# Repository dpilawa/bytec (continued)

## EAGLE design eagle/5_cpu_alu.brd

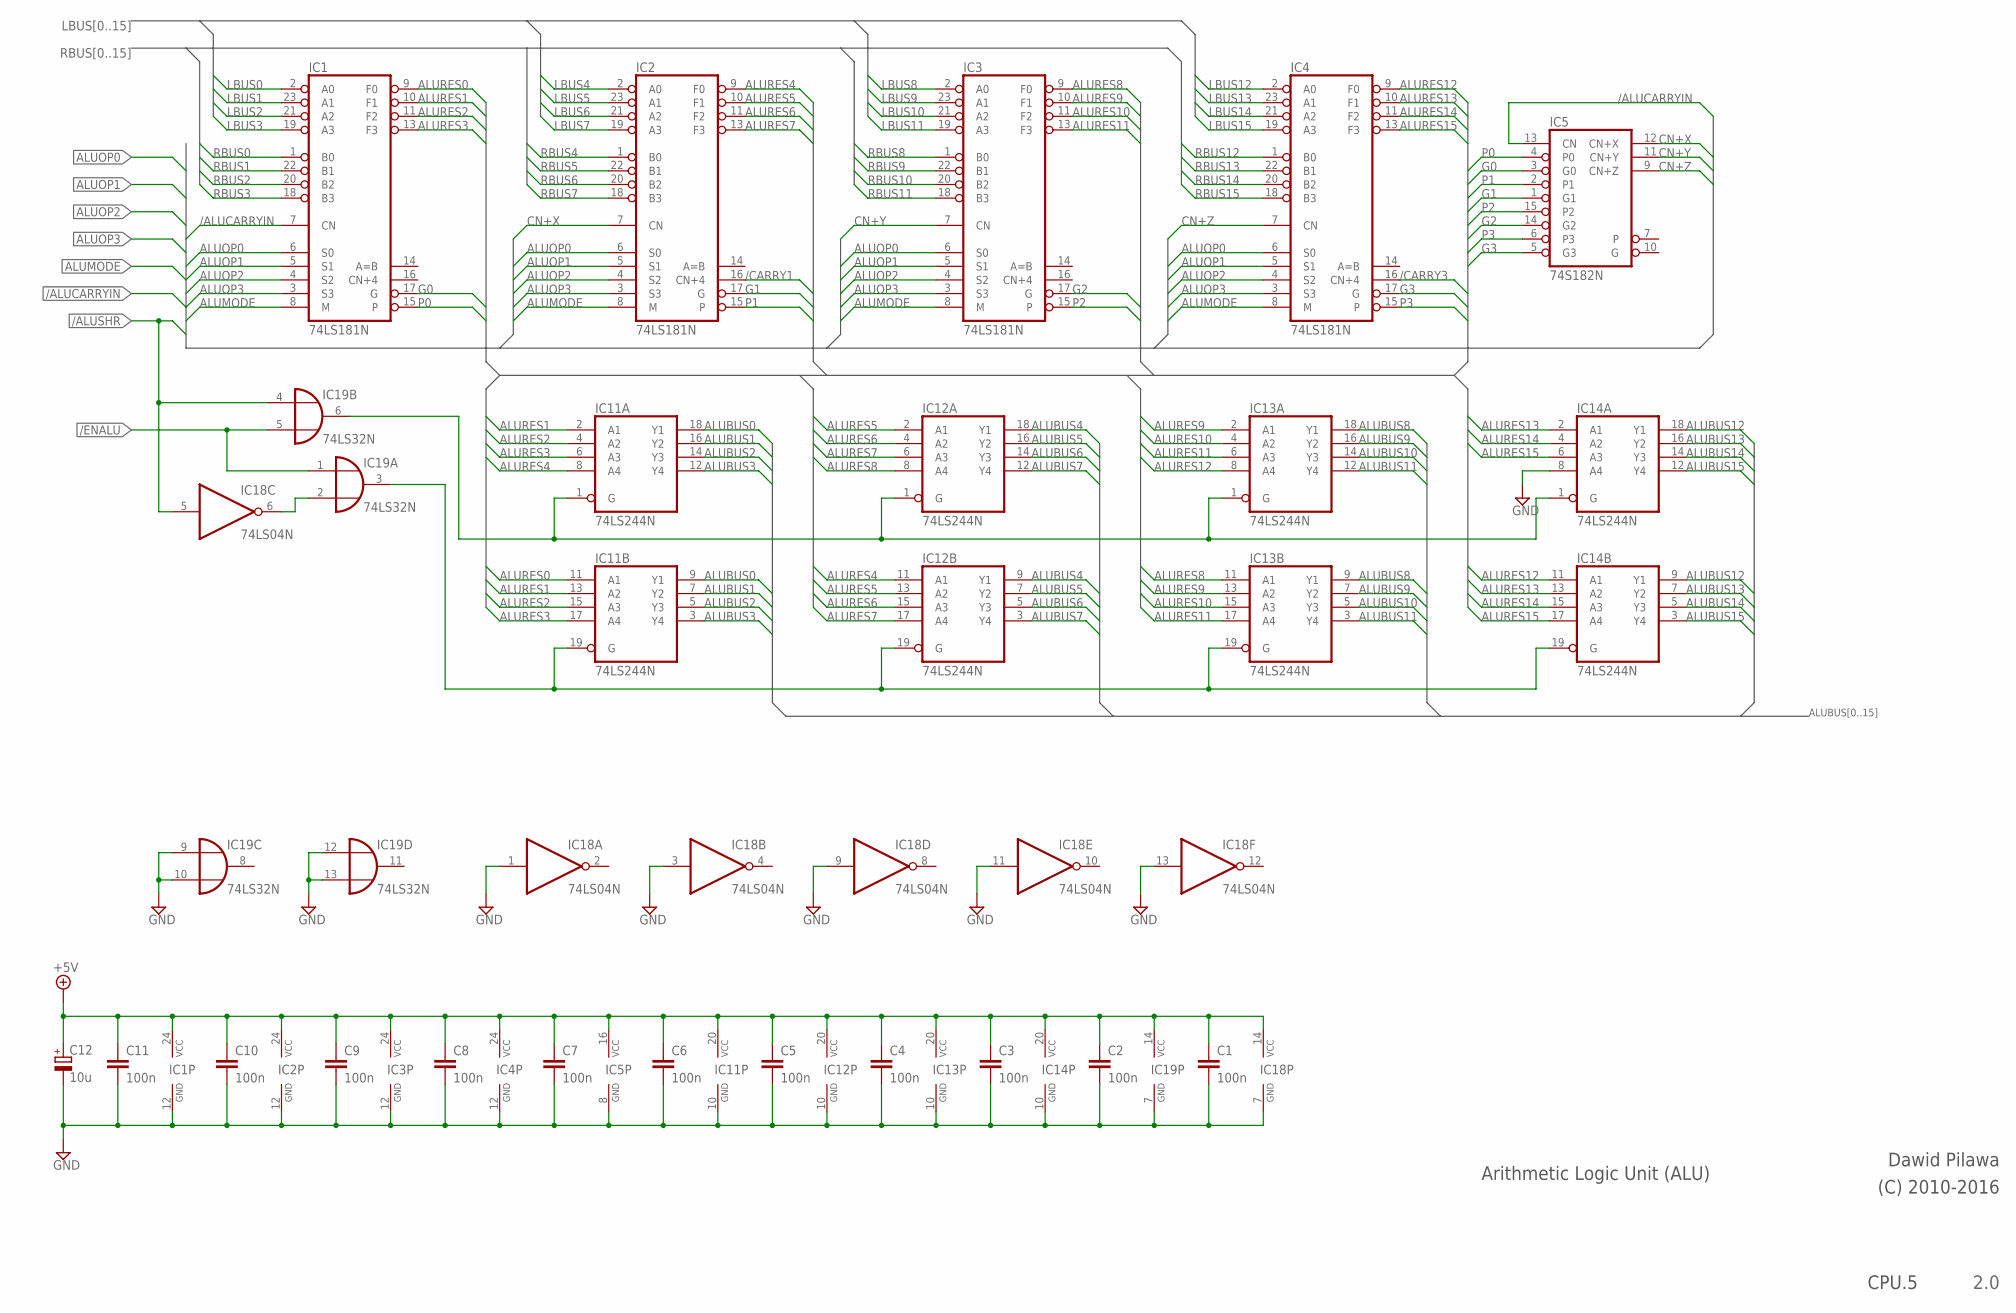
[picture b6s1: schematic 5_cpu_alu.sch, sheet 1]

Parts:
C1, C2, C3, C4, C5, C6, C7, C8, C9, C10, C11: 100n; C050-024X044
C12: 10u; E2,5-6
IC1, IC2, IC3, IC4: 74LS181N; DIL24-6
IC5: 74S182N; DIL16
IC11, IC12, IC13, IC14: 74LS244N; DIL20
IC18: 74LS04N; DIL14
IC19: 74LS32N; DIL14

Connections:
+5V: C1.1, C2.1, C3.1, C4.1, C5.1, C6.1, C7.1, C8.1, C9.1, C10.1, C11.1, C12.+, IC1.24 (VCC), IC2.24 (VCC), IC3.24 (VCC), IC4.24 (VCC), IC5.16 (VCC), IC11.20 (VCC), IC12.20 (VCC), IC13.20 (VCC), IC14.20 (VCC), IC18.14 (VCC), IC19.14 (VCC); also elsewhere on the board
/ALUCARRYIN: IC1.7 (CN), IC5.13 (CN); also elsewhere on the board
/ALUSHR: IC18.5 (I), IC19.4 (I0); also elsewhere on the board
/CARRY1: IC2.16 (CN+4); also elsewhere on the board
/CARRY3: IC4.16 (CN+4); also elsewhere on the board
/ENALU: IC19.1 (I0), IC19.5 (I1); also elsewhere on the board
ALUBUS0: IC11.9 (Y1), IC11.18 (Y1); also elsewhere on the board
ALUBUS1: IC11.7 (Y2), IC11.16 (Y2); also elsewhere on the board
ALUBUS2: IC11.5 (Y3), IC11.14 (Y3); also elsewhere on the board
ALUBUS3: IC11.3 (Y4), IC11.12 (Y4); also elsewhere on the board
ALUBUS4: IC12.9 (Y1), IC12.18 (Y1); also elsewhere on the board
ALUBUS5: IC12.7 (Y2), IC12.16 (Y2); also elsewhere on the board
ALUBUS6: IC12.5 (Y3), IC12.14 (Y3); also elsewhere on the board
ALUBUS7: IC12.3 (Y4), IC12.12 (Y4); also elsewhere on the board
ALUBUS8: IC13.9 (Y1), IC13.18 (Y1); also elsewhere on the board
ALUBUS9: IC13.7 (Y2), IC13.16 (Y2); also elsewhere on the board
ALUBUS10: IC13.5 (Y3), IC13.14 (Y3); also elsewhere on the board
ALUBUS11: IC13.3 (Y4), IC13.12 (Y4); also elsewhere on the board
ALUBUS12: IC14.9 (Y1), IC14.18 (Y1); also elsewhere on the board
ALUBUS13: IC14.7 (Y2), IC14.16 (Y2); also elsewhere on the board
ALUBUS14: IC14.5 (Y3), IC14.14 (Y3); also elsewhere on the board
ALUBUS15: IC14.3 (Y4), IC14.12 (Y4); also elsewhere on the board
ALUMODE: IC1.8 (M), IC2.8 (M), IC3.8 (M), IC4.8 (M); also elsewhere on the board
ALUOP0: IC1.6 (S0), IC2.6 (S0), IC3.6 (S0), IC4.6 (S0); also elsewhere on the board
ALUOP1: IC1.5 (S1), IC2.5 (S1), IC3.5 (S1), IC4.5 (S1); also elsewhere on the board
ALUOP2: IC1.4 (S2), IC2.4 (S2), IC3.4 (S2), IC4.4 (S2); also elsewhere on the board
ALUOP3: IC1.3 (S3), IC2.3 (S3), IC3.3 (S3), IC4.3 (S3); also elsewhere on the board
ALURES0: IC1.9 (F0), IC11.11 (A1); also elsewhere on the board
ALURES1: IC1.10 (F1), IC11.2 (A1), IC11.13 (A2)
ALURES2: IC1.11 (F2), IC11.4 (A2), IC11.15 (A3)
ALURES3: IC1.13 (F3), IC11.6 (A3), IC11.17 (A4)
ALURES4: IC2.9 (F0), IC11.8 (A4), IC12.11 (A1)
ALURES5: IC2.10 (F1), IC12.2 (A1), IC12.13 (A2)
ALURES6: IC2.11 (F2), IC12.4 (A2), IC12.15 (A3)
ALURES7: IC2.13 (F3), IC12.6 (A3), IC12.17 (A4)
ALURES8: IC3.9 (F0), IC12.8 (A4), IC13.11 (A1); also elsewhere on the board
ALURES9: IC3.10 (F1), IC13.2 (A1), IC13.13 (A2)
ALURES10: IC3.11 (F2), IC13.4 (A2), IC13.15 (A3)
ALURES11: IC3.13 (F3), IC13.6 (A3), IC13.17 (A4)
ALURES12: IC4.9 (F0), IC13.8 (A4), IC14.11 (A1)
ALURES13: IC4.10 (F1), IC14.2 (A1), IC14.13 (A2)
ALURES14: IC4.11 (F2), IC14.4 (A2), IC14.15 (A3)
ALURES15: IC4.13 (F3), IC14.6 (A3), IC14.17 (A4)
CN+X: IC2.7 (CN), IC5.12 (CN+X)
CN+Y: IC3.7 (CN), IC5.11 (CN+Y)
CN+Z: IC4.7 (CN), IC5.9 (CN+Z)
G0: IC1.17 (G), IC5.3 (G0)
G1: IC2.17 (G), IC5.1 (G1)
G2: IC3.17 (G), IC5.14 (G2)
G3: IC4.17 (G), IC5.5 (G3)
GND: C1.2, C2.2, C3.2, C4.2, C5.2, C6.2, C7.2, C8.2, C9.2, C10.2, C11.2, C12.-, IC1.12 (GND), IC2.12 (GND), IC3.12 (GND), IC4.12 (GND), IC5.8 (GND), IC11.10 (GND), IC12.10 (GND), IC13.10 (GND), IC14.8 (A4), IC14.10 (GND), IC18.1 (I), IC18.3 (I), IC18.7 (GND), IC18.9 (I), IC18.11 (I), IC18.13 (I), IC19.7 (GND), IC19.9 (I0), IC19.10 (I1), IC19.12 (I0), IC19.13 (I1); also elsewhere on the board
LBUS0: IC1.2 (A0); also elsewhere on the board
LBUS1: IC1.23 (A1); also elsewhere on the board
LBUS2: IC1.21 (A2); also elsewhere on the board
LBUS3: IC1.19 (A3); also elsewhere on the board
LBUS4: IC2.2 (A0); also elsewhere on the board
LBUS5: IC2.23 (A1); also elsewhere on the board
LBUS6: IC2.21 (A2); also elsewhere on the board
LBUS7: IC2.19 (A3); also elsewhere on the board
LBUS8: IC3.2 (A0); also elsewhere on the board
LBUS9: IC3.23 (A1); also elsewhere on the board
LBUS10: IC3.21 (A2); also elsewhere on the board
LBUS11: IC3.19 (A3); also elsewhere on the board
LBUS12: IC4.2 (A0); also elsewhere on the board
LBUS13: IC4.23 (A1); also elsewhere on the board
LBUS14: IC4.21 (A2); also elsewhere on the board
LBUS15: IC4.19 (A3); also elsewhere on the board
unnamed: IC11.1 (G), IC12.1 (G), IC13.1 (G), IC14.1 (G), IC19.6 (O)
unnamed: IC18.6 (O), IC19.2 (I1)
unnamed: IC11.19 (G), IC12.19 (G), IC13.19 (G), IC14.19 (G), IC19.3 (O)
P0: IC1.15, IC5.4 (P0)
P1: IC2.15, IC5.2 (P1)
P2: IC3.15, IC5.15 (P2)
P3: IC4.15, IC5.6 (P3)
RBUS0: IC1.1 (B0); also elsewhere on the board
RBUS1: IC1.22 (B1); also elsewhere on the board
RBUS2: IC1.20 (B2); also elsewhere on the board
RBUS3: IC1.18 (B3); also elsewhere on the board
RBUS4: IC2.1 (B0); also elsewhere on the board
RBUS5: IC2.22 (B1); also elsewhere on the board
RBUS6: IC2.20 (B2); also elsewhere on the board
RBUS7: IC2.18 (B3); also elsewhere on the board
RBUS8: IC3.1 (B0); also elsewhere on the board
RBUS9: IC3.22 (B1); also elsewhere on the board
RBUS10: IC3.20 (B2); also elsewhere on the board
RBUS11: IC3.18 (B3); also elsewhere on the board
RBUS12: IC4.1 (B0); also elsewhere on the board
RBUS13: IC4.22 (B1); also elsewhere on the board
RBUS14: IC4.20 (B2); also elsewhere on the board
RBUS15: IC4.18 (B3); also elsewhere on the board

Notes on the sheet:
Arithmetic Logic Unit (ALU)
Dawid Pilawa
(C) 2010-2016
2.0
CPU.5

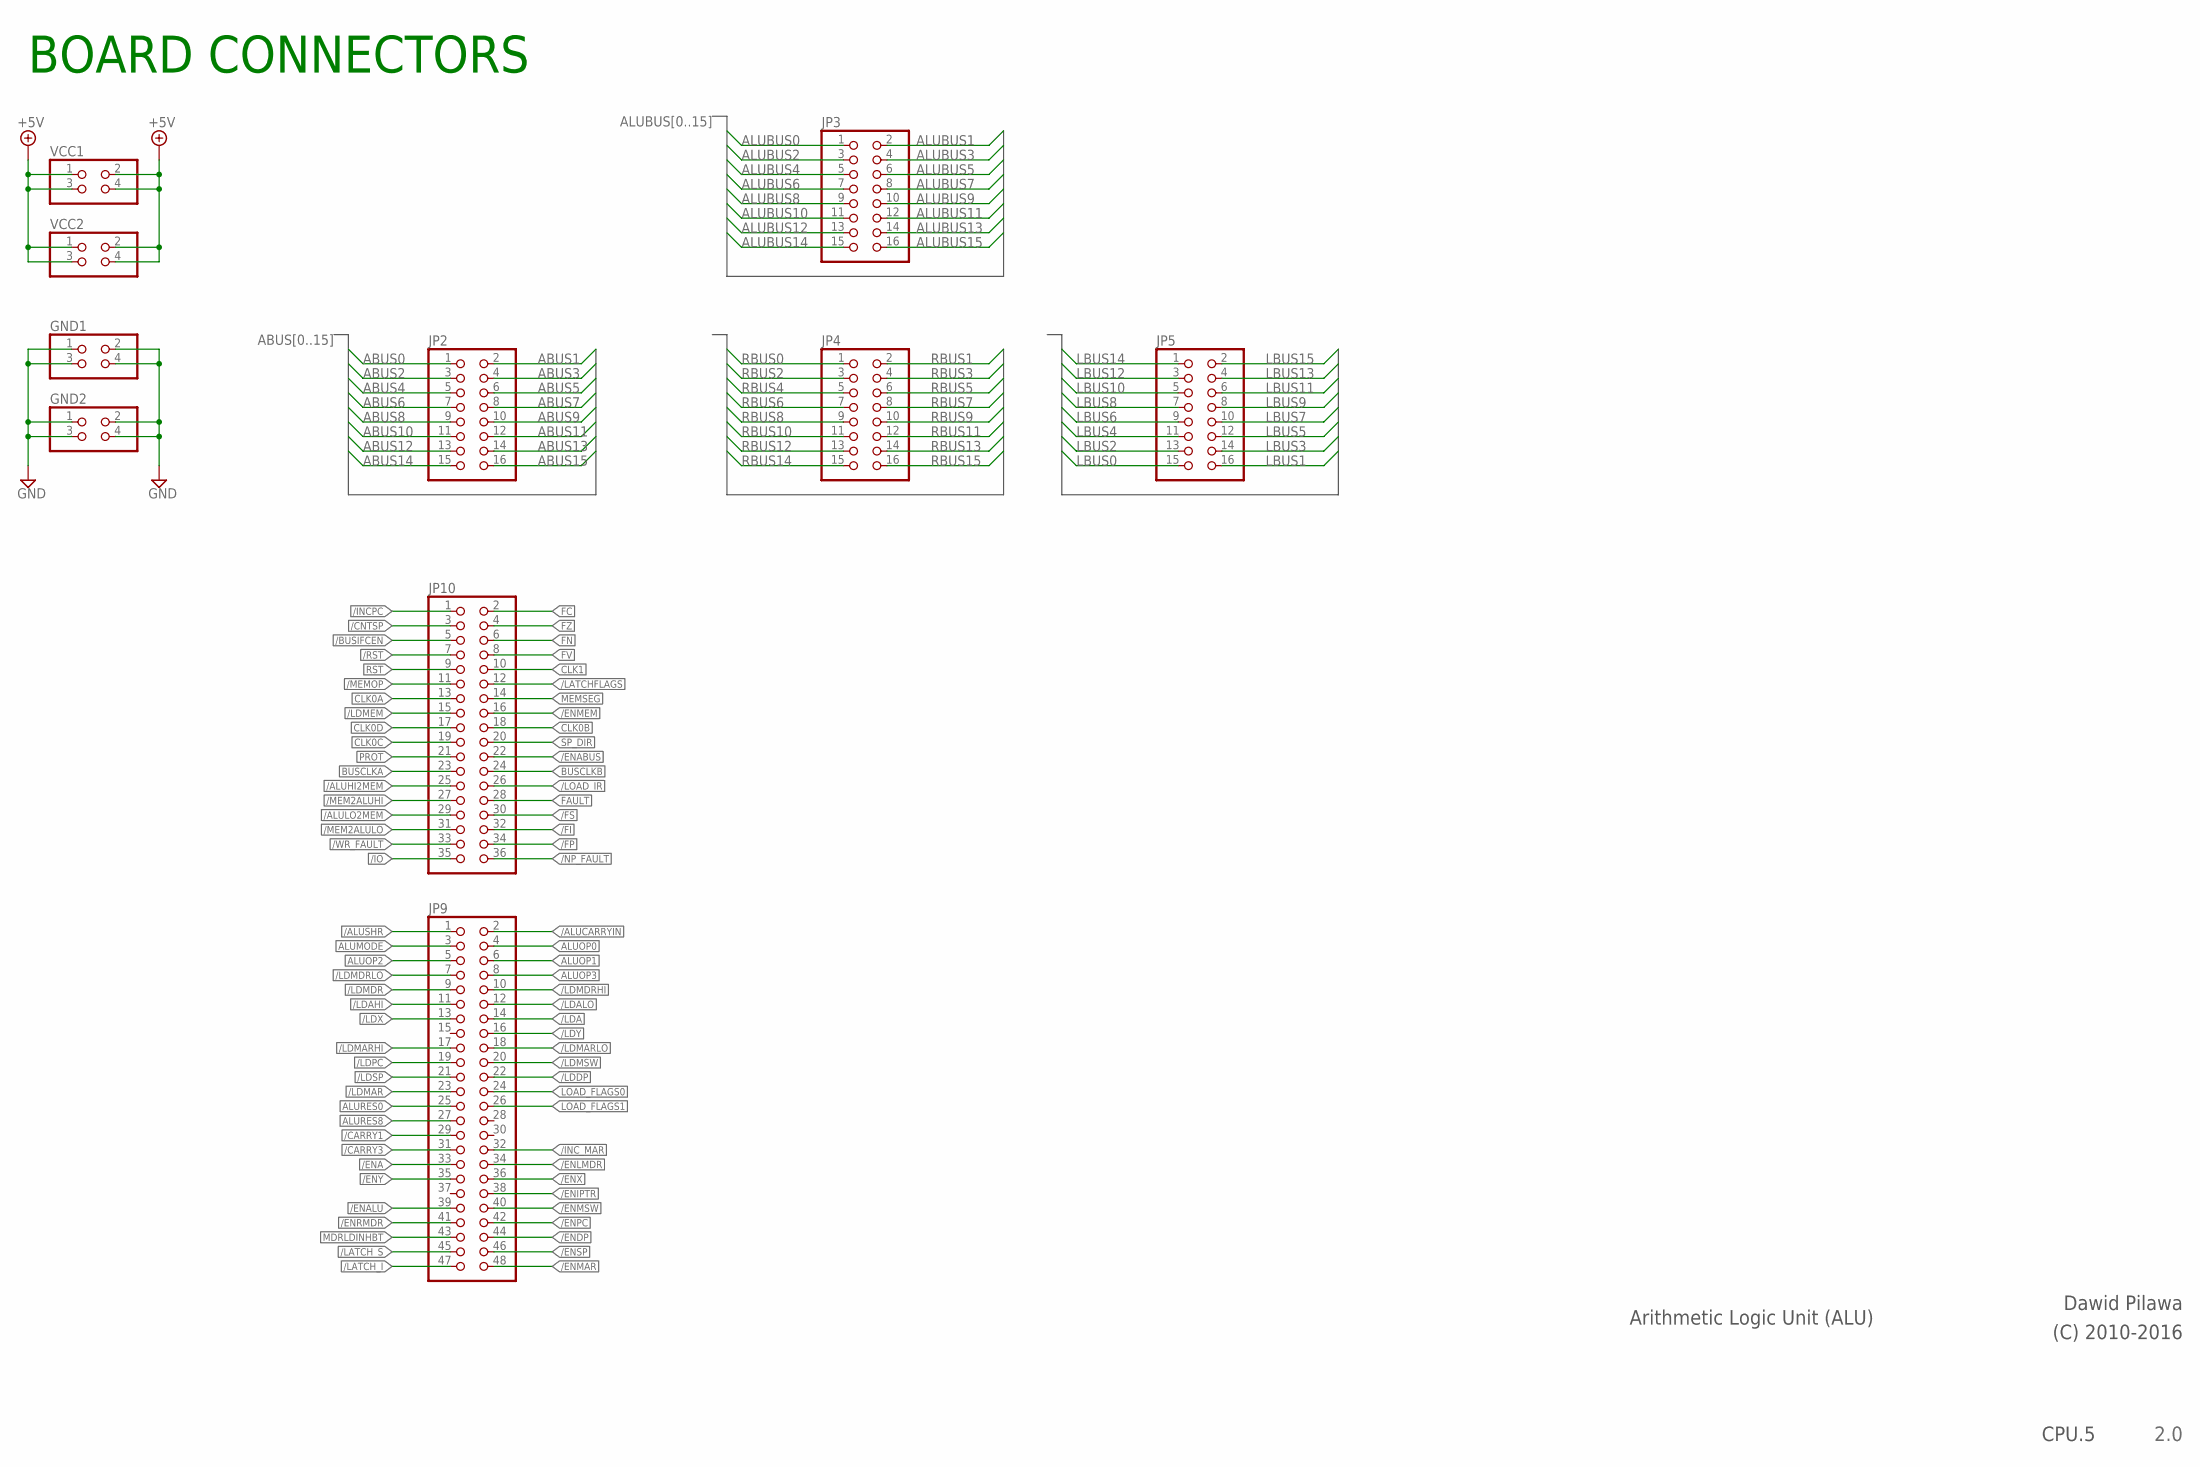
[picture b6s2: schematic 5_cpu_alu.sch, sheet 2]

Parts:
GND1, GND2: PINHD-2X2; 2X02
JP2, JP3, JP4, JP5: PINHD-2X8; 2X08
JP9: PINHD-2X24; 2X24
JP10: PINHD-2X18; 2X18
VCC1, VCC2: PINHD-2X2; 2X02

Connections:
+5V: VCC1.1, VCC1.2, VCC1.3, VCC1.4, VCC2.1, VCC2.2, VCC2.3, VCC2.4; also elsewhere on the board
/ALUCARRYIN: JP9.2; also elsewhere on the board
/ALUHI2MEM: JP10.25
/ALULO2MEM: JP10.29
/ALUSHR: JP9.1; also elsewhere on the board
/BUSIFCEN: JP10.5
/CARRY1: JP9.29; also elsewhere on the board
/CARRY3: JP9.31; also elsewhere on the board
/CNTSP: JP10.3
/ENA: JP9.33
/ENABUS: JP10.22
/ENALU: JP9.39; also elsewhere on the board
/ENDP: JP9.44
/ENIPTR: JP9.38
/ENLMDR: JP9.34
/ENMAR: JP9.48
/ENMEM: JP10.16
/ENMSW: JP9.40
/ENPC: JP9.42
/ENRMDR: JP9.41
/ENSP: JP9.46
/ENX: JP9.36
/ENY: JP9.35
/FI: JP10.32
/FP: JP10.34
/FS: JP10.30
/INCPC: JP10.1
/INC_MAR: JP9.32
/IO: JP10.35
/LATCHFLAGS: JP10.12
/LATCH_I: JP9.47
/LATCH_S: JP9.45
/LDA: JP9.14
/LDAHI: JP9.11
/LDALO: JP9.12
/LDDP: JP9.22
/LDMAR: JP9.23
/LDMARHI: JP9.17
/LDMARLO: JP9.18
/LDMDR: JP9.9
/LDMDRHI: JP9.10
/LDMDRLO: JP9.7
/LDMEM: JP10.15
/LDMSW: JP9.20
/LDPC: JP9.19
/LDSP: JP9.21
/LDX: JP9.13
/LDY: JP9.16
/LOAD_IR: JP10.26
/MEM2ALUHI: JP10.27
/MEM2ALULO: JP10.31
/MEMOP: JP10.11
/NP_FAULT: JP10.36
/RST: JP10.7
/WR_FAULT: JP10.33
ABUS0: JP2.1
ABUS1: JP2.2
ABUS2: JP2.3
ABUS3: JP2.4
ABUS4: JP2.5
ABUS5: JP2.6
ABUS6: JP2.7
ABUS7: JP2.8
ABUS8: JP2.9
ABUS9: JP2.10
ABUS10: JP2.11
ABUS11: JP2.12
ABUS12: JP2.13
ABUS13: JP2.14
ABUS14: JP2.15
ABUS15: JP2.16
ALUBUS0: JP3.1; also elsewhere on the board
ALUBUS1: JP3.2; also elsewhere on the board
ALUBUS2: JP3.3; also elsewhere on the board
ALUBUS3: JP3.4; also elsewhere on the board
ALUBUS4: JP3.5; also elsewhere on the board
ALUBUS5: JP3.6; also elsewhere on the board
ALUBUS6: JP3.7; also elsewhere on the board
ALUBUS7: JP3.8; also elsewhere on the board
ALUBUS8: JP3.9; also elsewhere on the board
ALUBUS9: JP3.10; also elsewhere on the board
ALUBUS10: JP3.11; also elsewhere on the board
ALUBUS11: JP3.12; also elsewhere on the board
ALUBUS12: JP3.13; also elsewhere on the board
ALUBUS13: JP3.14; also elsewhere on the board
ALUBUS14: JP3.15; also elsewhere on the board
ALUBUS15: JP3.16; also elsewhere on the board
ALUMODE: JP9.3; also elsewhere on the board
ALUOP0: JP9.4; also elsewhere on the board
ALUOP1: JP9.6; also elsewhere on the board
ALUOP2: JP9.5; also elsewhere on the board
ALUOP3: JP9.8; also elsewhere on the board
ALURES0: JP9.25; also elsewhere on the board
ALURES8: JP9.27; also elsewhere on the board
BUSCLKA: JP10.23
BUSCLKB: JP10.24
CLK0A: JP10.13
CLK0B: JP10.18
CLK0C: JP10.19
CLK0D: JP10.17
CLK1: JP10.10
FAULT: JP10.28
FC: JP10.2
FN: JP10.6
FV: JP10.8
FZ: JP10.4
GND: GND1.1, GND1.2, GND1.3, GND1.4, GND2.1, GND2.2, GND2.3, GND2.4; also elsewhere on the board
LBUS0: JP5.15; also elsewhere on the board
LBUS1: JP5.16; also elsewhere on the board
LBUS2: JP5.13; also elsewhere on the board
LBUS3: JP5.14; also elsewhere on the board
LBUS4: JP5.11; also elsewhere on the board
LBUS5: JP5.12; also elsewhere on the board
LBUS6: JP5.9; also elsewhere on the board
LBUS7: JP5.10; also elsewhere on the board
LBUS8: JP5.7; also elsewhere on the board
LBUS9: JP5.8; also elsewhere on the board
LBUS10: JP5.5; also elsewhere on the board
LBUS11: JP5.6; also elsewhere on the board
LBUS12: JP5.3; also elsewhere on the board
LBUS13: JP5.4; also elsewhere on the board
LBUS14: JP5.1; also elsewhere on the board
LBUS15: JP5.2; also elsewhere on the board
LOAD_FLAGS0: JP9.24
LOAD_FLAGS1: JP9.26
MDRLDINHBT: JP9.43
MEMSEG: JP10.14
PROT: JP10.21
RBUS0: JP4.1; also elsewhere on the board
RBUS1: JP4.2; also elsewhere on the board
RBUS2: JP4.3; also elsewhere on the board
RBUS3: JP4.4; also elsewhere on the board
RBUS4: JP4.5; also elsewhere on the board
RBUS5: JP4.6; also elsewhere on the board
RBUS6: JP4.7; also elsewhere on the board
RBUS7: JP4.8; also elsewhere on the board
RBUS8: JP4.9; also elsewhere on the board
RBUS9: JP4.10; also elsewhere on the board
RBUS10: JP4.11; also elsewhere on the board
RBUS11: JP4.12; also elsewhere on the board
RBUS12: JP4.13; also elsewhere on the board
RBUS13: JP4.14; also elsewhere on the board
RBUS14: JP4.15; also elsewhere on the board
RBUS15: JP4.16; also elsewhere on the board
RST: JP10.9
SP_DIR: JP10.20

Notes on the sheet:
Arithmetic Logic Unit (ALU)
Dawid Pilawa
(C) 2010-2016
2.0
CPU.5
BOARD CONNECTORS

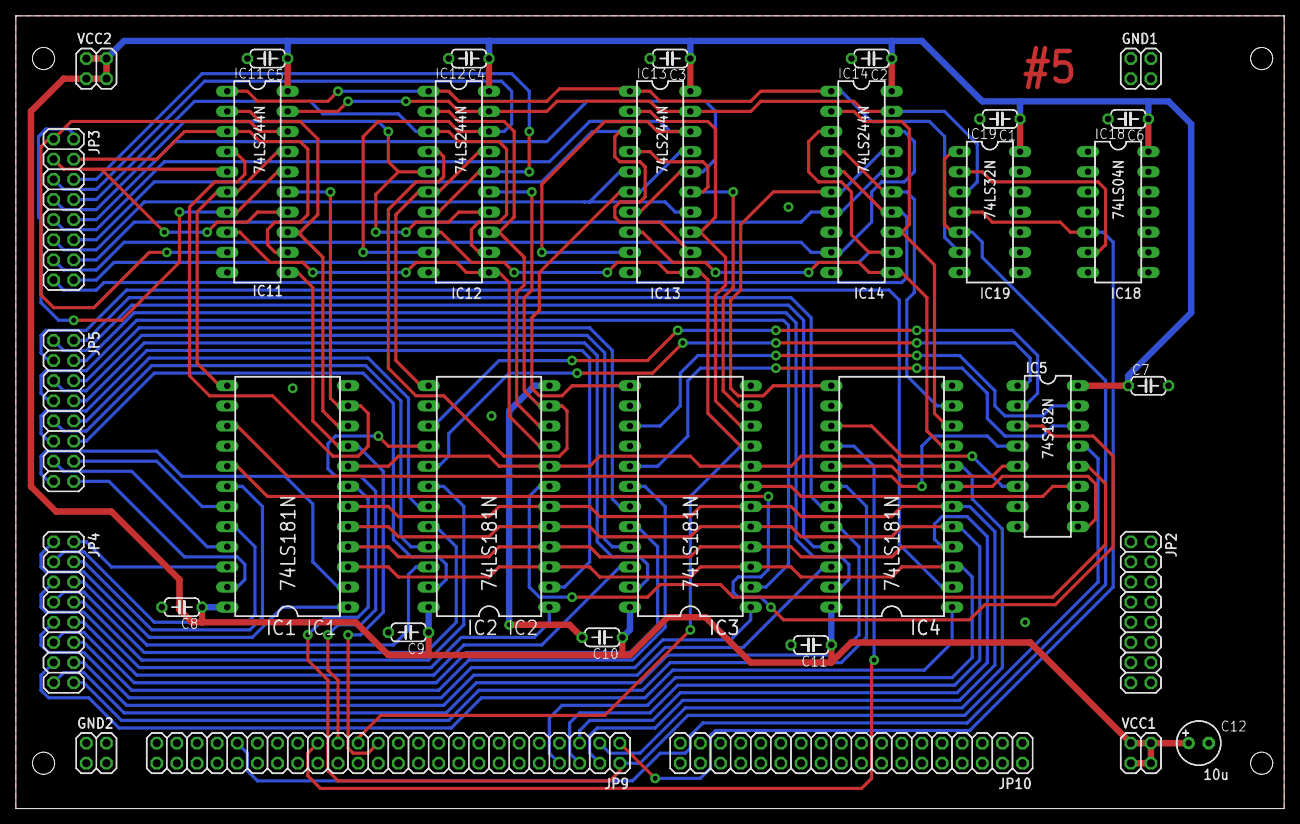
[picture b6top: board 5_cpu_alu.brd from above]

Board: 2 copper layers, 160.0 x 100.0 mm, 33 parts (0 on the bottom side), 90 nets.

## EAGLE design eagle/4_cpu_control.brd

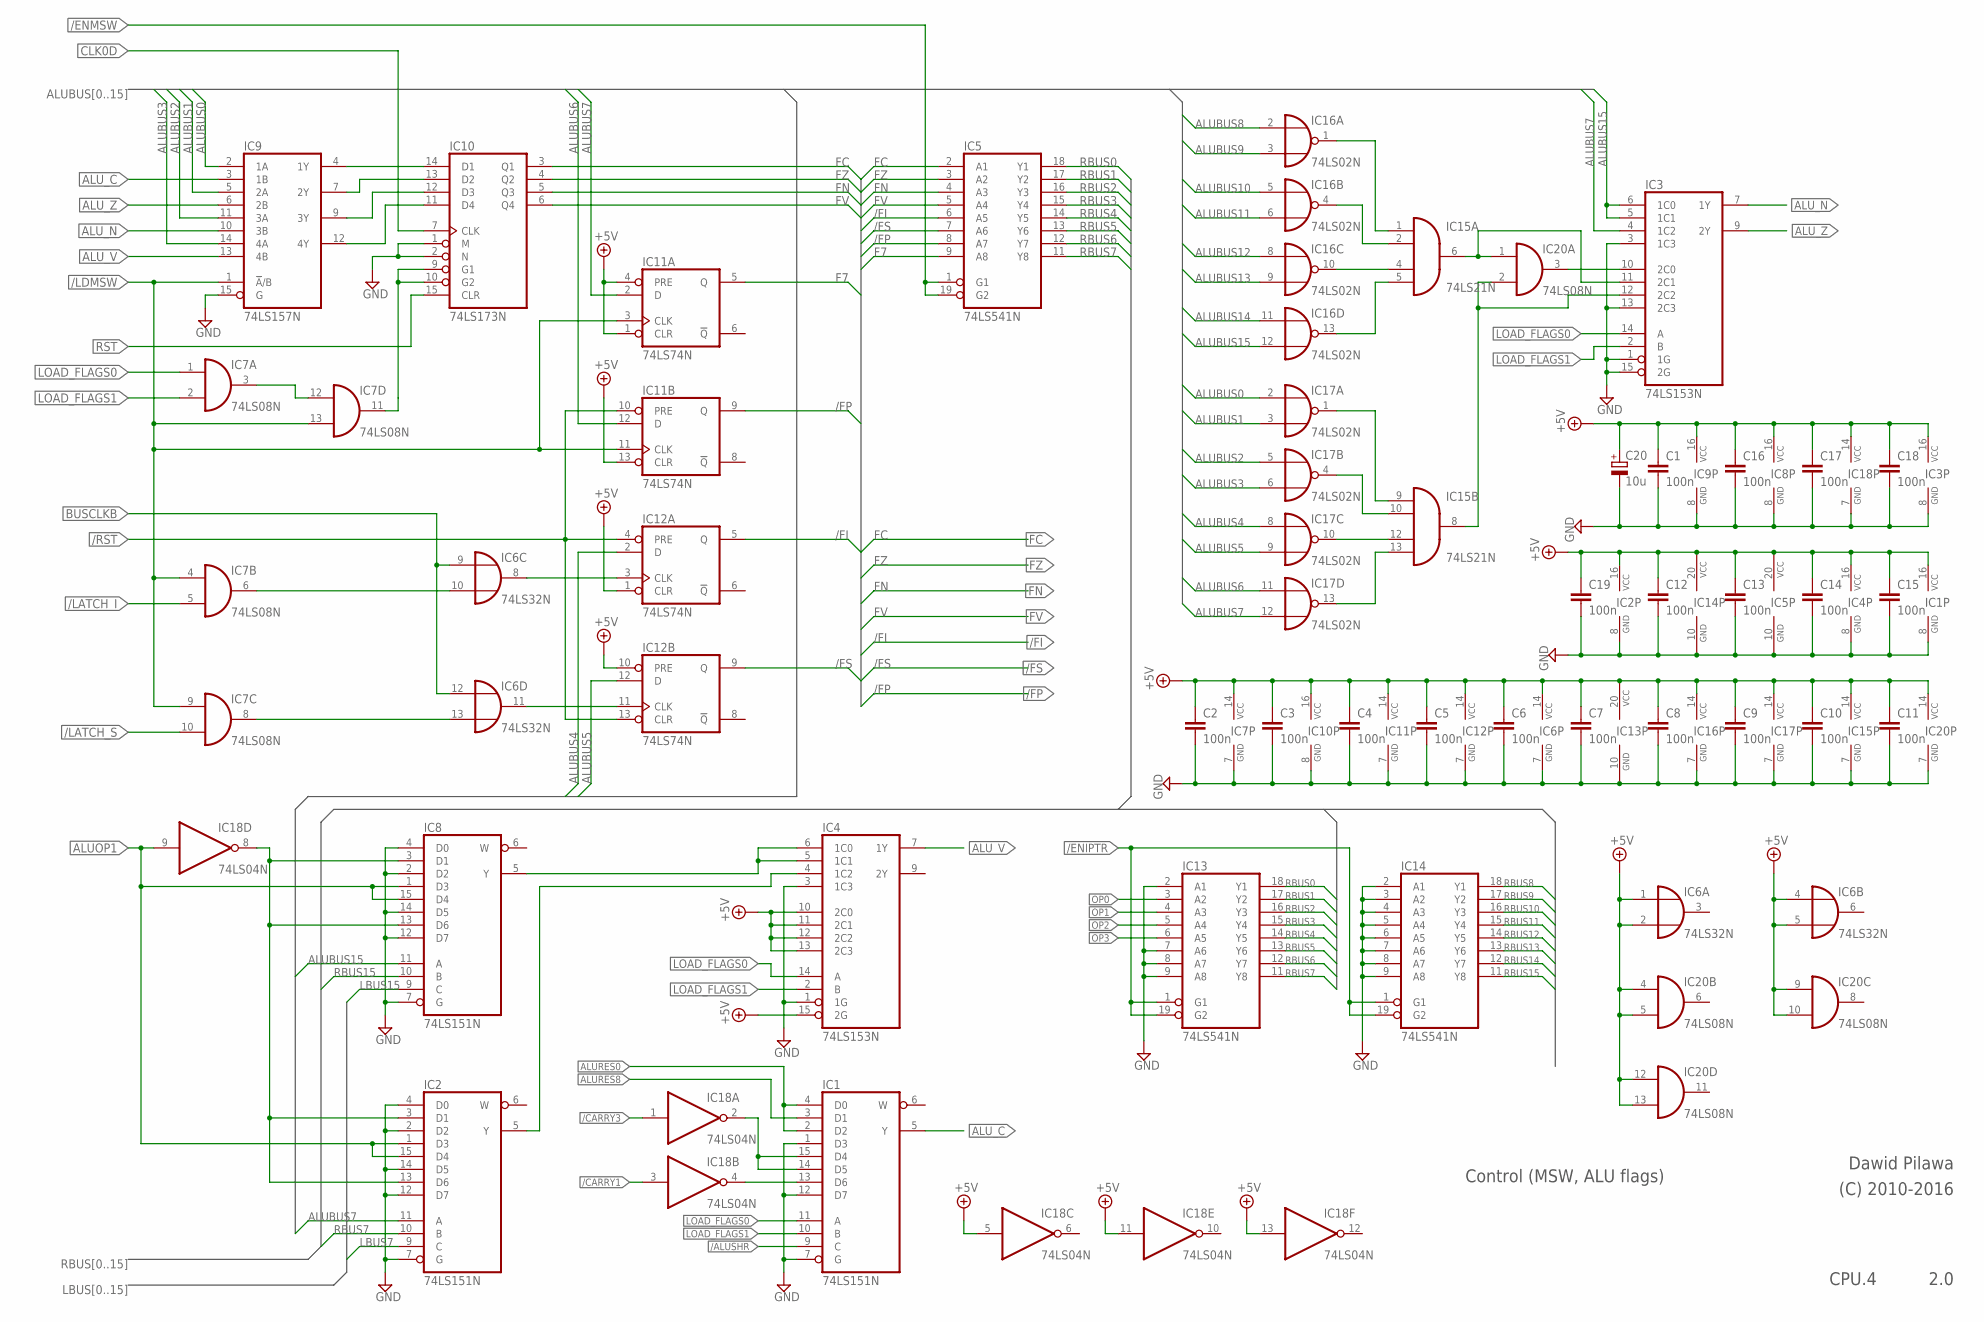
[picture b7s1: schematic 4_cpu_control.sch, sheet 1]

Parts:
C1, C2, C3, C4, C5, C6, C7, C8, C9, C10, C11, C12, C13, C14, C15, C16, C17, C18, C19: 100n; C050-024X044
C20: 10u; E2,5-6
IC1, IC2, IC8: 74LS151N; DIL16
IC3, IC4: 74LS153N; DIL16
IC5, IC13, IC14: 74LS541N; DIL20
IC6: 74LS32N; DIL14
IC7, IC20: 74LS08N; DIL14
IC9: 74LS157N; DIL16
IC10: 74LS173N; DIL16
IC11, IC12: 74LS74N; DIL14
IC15: 74LS21N; DIL14
IC16, IC17: 74LS02N; DIL14
IC18: 74LS04N; DIL14

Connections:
+5V: C1.1, C2.1, C3.1, C4.1, C5.1, C6.1, C7.1, C8.1, C9.1, C10.1, C11.1, C12.1, C13.1, C14.1, C15.1, C16.1, C17.1, C18.1, C19.1, C20.+, IC1.16 (VCC), IC2.16 (VCC), IC3.16 (VCC), IC4.10 (2C0), IC4.11 (2C1), IC4.12 (2C2), IC4.13 (2C3), IC4.15 (2G), IC4.16 (VCC), IC5.20 (VCC), IC6.1 (I0), IC6.2 (I1), IC6.4 (I0), IC6.5 (I1), IC6.14 (VCC), IC7.14 (VCC), IC8.16 (VCC), IC9.16 (VCC), IC10.16 (VCC), IC11.1 (CLR), IC11.4 (PRE), IC11.13 (CLR), IC11.14 (VCC), IC12.1 (CLR), IC12.10 (PRE), IC12.14 (VCC), IC13.20 (VCC), IC14.20 (VCC), IC15.14 (VCC), IC16.14 (VCC), IC17.14 (VCC), IC18.5 (I), IC18.11 (I), IC18.13 (I), IC18.14 (VCC), IC20.4 (I0), IC20.5 (I1), IC20.9 (I0), IC20.10 (I1), IC20.12 (I0), IC20.13 (I1), IC20.14 (VCC); also elsewhere on the board
/ALUSHR: IC1.9 (C); also elsewhere on the board
/CARRY1: IC18.3 (I); also elsewhere on the board
/CARRY3: IC18.1 (I); also elsewhere on the board
/ENIPTR: IC13.1 (G1), IC13.19 (G2), IC14.1 (G1), IC14.19 (G2); also elsewhere on the board
/ENMSW: IC5.1 (G1), IC5.19 (G2); also elsewhere on the board
/FI: IC5.6 (A5), IC12.5 (Q); also elsewhere on the board
/FP: IC5.8 (A7), IC11.9 (Q); also elsewhere on the board
/FS: IC5.7 (A6), IC12.9 (Q); also elsewhere on the board
/LATCH_I: IC7.5 (I1); also elsewhere on the board
/LATCH_S: IC7.10 (I1); also elsewhere on the board
/LDMSW: IC7.4 (I0), IC7.9 (I0), IC7.13 (I1), IC9.1 (!A!/B), IC11.3 (CLK), IC11.11 (CLK); also elsewhere on the board
/RST: IC11.10 (PRE), IC12.4 (PRE), IC12.13 (CLR); also elsewhere on the board
ALUBUS0: IC9.2 (1A), IC17.2 (I0); also elsewhere on the board
ALUBUS1: IC9.5 (2A), IC17.3 (I1); also elsewhere on the board
ALUBUS2: IC9.11 (3A), IC17.5 (I0); also elsewhere on the board
ALUBUS3: IC9.14 (4A), IC17.6 (I1); also elsewhere on the board
ALUBUS4: IC12.2 (D), IC17.8 (I0); also elsewhere on the board
ALUBUS5: IC12.12 (D), IC17.9 (I1); also elsewhere on the board
ALUBUS6: IC11.12 (D), IC17.11 (I0); also elsewhere on the board
ALUBUS7: IC2.11 (A), IC3.4 (1C2), IC11.2 (D), IC17.12 (I1); also elsewhere on the board
ALUBUS8: IC16.2 (I0); also elsewhere on the board
ALUBUS9: IC16.3 (I1); also elsewhere on the board
ALUBUS10: IC16.5 (I0); also elsewhere on the board
ALUBUS11: IC16.6 (I1); also elsewhere on the board
ALUBUS12: IC16.8 (I0); also elsewhere on the board
ALUBUS13: IC16.9 (I1); also elsewhere on the board
ALUBUS14: IC16.11 (I0); also elsewhere on the board
ALUBUS15: IC3.5 (1C1), IC3.6 (1C0), IC8.11 (A), IC16.12 (I1); also elsewhere on the board
ALUOP1: IC2.1 (D3), IC2.15 (D4), IC8.1 (D3), IC8.15 (D4), IC18.9 (I); also elsewhere on the board
ALURES0: IC1.2 (D2), IC1.4 (D0); also elsewhere on the board
ALURES8: IC1.3 (D1); also elsewhere on the board
ALU_C: IC1.5 (Y), IC9.3 (1B)
ALU_N: IC3.7 (1Y), IC9.10 (3B)
ALU_V: IC4.7 (1Y), IC9.13 (4B)
ALU_Z: IC3.9 (2Y), IC9.6 (2B)
BUSCLKB: IC6.9 (I0), IC6.12 (I0); also elsewhere on the board
CLK0D: IC10.7 (CLK); also elsewhere on the board
F7: IC5.9 (A8), IC11.5 (Q)
FC: IC5.2 (A1), IC10.3 (Q1); also elsewhere on the board
FN: IC5.4 (A3), IC10.5 (Q3); also elsewhere on the board
FV: IC5.5 (A4), IC10.6 (Q4); also elsewhere on the board
FZ: IC5.3 (A2), IC10.4 (Q2); also elsewhere on the board
GND: C1.2, C2.2, C3.2, C4.2, C5.2, C6.2, C7.2, C8.2, C9.2, C10.2, C11.2, C12.2, C13.2, C14.2, C15.2, C16.2, C17.2, C18.2, C19.2, C20.-, IC1.1 (D3), IC1.7 (G), IC1.8 (GND), IC1.12 (D7), IC2.2 (D2), IC2.4 (D0), IC2.7 (G), IC2.8 (GND), IC2.12 (D7), IC2.14 (D5), IC3.1 (1G), IC3.3 (1C3), IC3.8 (GND), IC3.13 (2C3), IC3.15 (2G), IC4.1 (1G), IC4.3 (1C3), IC4.8 (GND), IC5.10 (GND), IC6.7 (GND), IC7.7 (GND), IC8.2 (D2), IC8.4 (D0), IC8.7 (G), IC8.8 (GND), IC8.12 (D7), IC8.14 (D5), IC9.8 (GND), IC9.15 (G), IC10.1 (M), IC10.2 (N), IC10.8 (GND), IC11.7 (GND), IC12.7 (GND), IC13.2 (A1), IC13.7 (A6), IC13.8 (A7), IC13.9 (A8), IC13.10 (GND), IC14.2 (A1), IC14.3 (A2), IC14.4 (A3), IC14.5 (A4), IC14.6 (A5), IC14.7 (A6), IC14.8 (A7), IC14.9 (A8), IC14.10 (GND), IC15.7 (GND), IC16.7 (GND), IC17.7 (GND), IC18.7 (GND), IC20.7 (GND); also elsewhere on the board
LBUS7: IC2.9 (C); also elsewhere on the board
LBUS15: IC8.9 (C); also elsewhere on the board
LOAD_FLAGS0: IC1.11 (A), IC3.14 (A), IC4.14 (A), IC7.1 (I0); also elsewhere on the board
LOAD_FLAGS1: IC1.10 (B), IC3.2 (B), IC4.2 (B), IC7.2 (I1); also elsewhere on the board
unnamed: IC4.5 (1C1), IC4.6 (1C0), IC8.5 (Y)
unnamed: IC1.13 (D6), IC18.4 (O)
unnamed: IC1.14 (D5), IC1.15 (D4), IC18.2 (O)
unnamed: IC15.1 (I0), IC16.1 (O)
unnamed: IC15.2 (I1), IC16.4 (O)
unnamed: IC15.4 (I2), IC16.10 (O)
unnamed: IC15.5 (I3), IC16.13 (O)
unnamed: IC15.9 (I0), IC17.1 (O)
unnamed: IC15.10 (I1), IC17.4 (O)
unnamed: IC15.12 (I2), IC17.10 (O)
unnamed: IC15.13 (I3), IC17.13 (O)
unnamed: IC3.11 (2C1), IC15.6 (O), IC20.1 (I0)
unnamed: IC3.12 (2C2), IC15.8 (O), IC20.2 (I1)
unnamed: IC3.10 (2C0), IC20.3 (O)
unnamed: IC7.11 (O), IC10.9 (G1), IC10.10 (G2)
unnamed: IC2.5 (Y), IC4.4 (1C2)
unnamed: IC2.3 (D1), IC2.13 (D6), IC8.3 (D1), IC8.13 (D6), IC18.8 (O)
unnamed: IC9.4 (1Y), IC10.14 (D1)
unnamed: IC9.7 (2Y), IC10.13 (D2)
unnamed: IC9.9 (3Y), IC10.12 (D3)
unnamed: IC9.12 (4Y), IC10.11 (D4)
unnamed: IC7.3 (O), IC7.12 (I0)
unnamed: IC6.8 (O), IC12.3 (CLK)
unnamed: IC6.11 (O), IC12.11 (CLK)
unnamed: IC6.10 (I1), IC7.6 (O)
unnamed: IC6.13 (I1), IC7.8 (O)
OP0: IC13.3 (A2); also elsewhere on the board
OP1: IC13.4 (A3); also elsewhere on the board
OP2: IC13.5 (A4); also elsewhere on the board
OP3: IC13.6 (A5); also elsewhere on the board
RBUS0: IC5.18 (Y1), IC13.18 (Y1); also elsewhere on the board
RBUS1: IC5.17 (Y2), IC13.17 (Y2); also elsewhere on the board
RBUS2: IC5.16 (Y3), IC13.16 (Y3); also elsewhere on the board
RBUS3: IC5.15 (Y4), IC13.15 (Y4); also elsewhere on the board
RBUS4: IC5.14 (Y5), IC13.14 (Y5); also elsewhere on the board
RBUS5: IC5.13 (Y6), IC13.13 (Y6); also elsewhere on the board
RBUS6: IC5.12 (Y7), IC13.12 (Y7); also elsewhere on the board
RBUS7: IC2.10 (B), IC5.11 (Y8), IC13.11 (Y8); also elsewhere on the board
RBUS8: IC14.18 (Y1); also elsewhere on the board
RBUS9: IC14.17 (Y2); also elsewhere on the board
RBUS10: IC14.16 (Y3); also elsewhere on the board
RBUS11: IC14.15 (Y4); also elsewhere on the board
RBUS12: IC14.14 (Y5); also elsewhere on the board
RBUS13: IC14.13 (Y6); also elsewhere on the board
RBUS14: IC14.12 (Y7); also elsewhere on the board
RBUS15: IC8.10 (B), IC14.11 (Y8); also elsewhere on the board
RST: IC10.15 (CLR); also elsewhere on the board

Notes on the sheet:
Control (MSW, ALU flags)
2.0
Dawid Pilawa
(C) 2010-2016
CPU.4
